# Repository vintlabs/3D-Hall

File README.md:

# 3D-Hall
3D Hall Effect Sensor Module - ALS31313 (Hardware)

This I²C sensor module cn detect magnetism in three dimensions (XYZ), and can be easily connect to a 3.3V Arduino, ESP32, Raspberry Pi or other microcontrollers. The header is designed such that it can plug directly into the header of a Raspberry Pi or and ESP32-Zip module. Board dimensions: 40mm x 15mm

The default I2C address is 0x60, but can be changed by modifying R3-R6 (See page 22 of the ALS31313 datasheet (https://www.allegromicro.com/~/media/Files/Datasheets/ALS31313-Datasheet.ashx).

Example Aruino sketch: https://github.com/vintlabs/ESP32-Arduino-3dHall-Example

Currently available on Amazon Canada: https://www.amazon.ca/dp/B0896VD73G

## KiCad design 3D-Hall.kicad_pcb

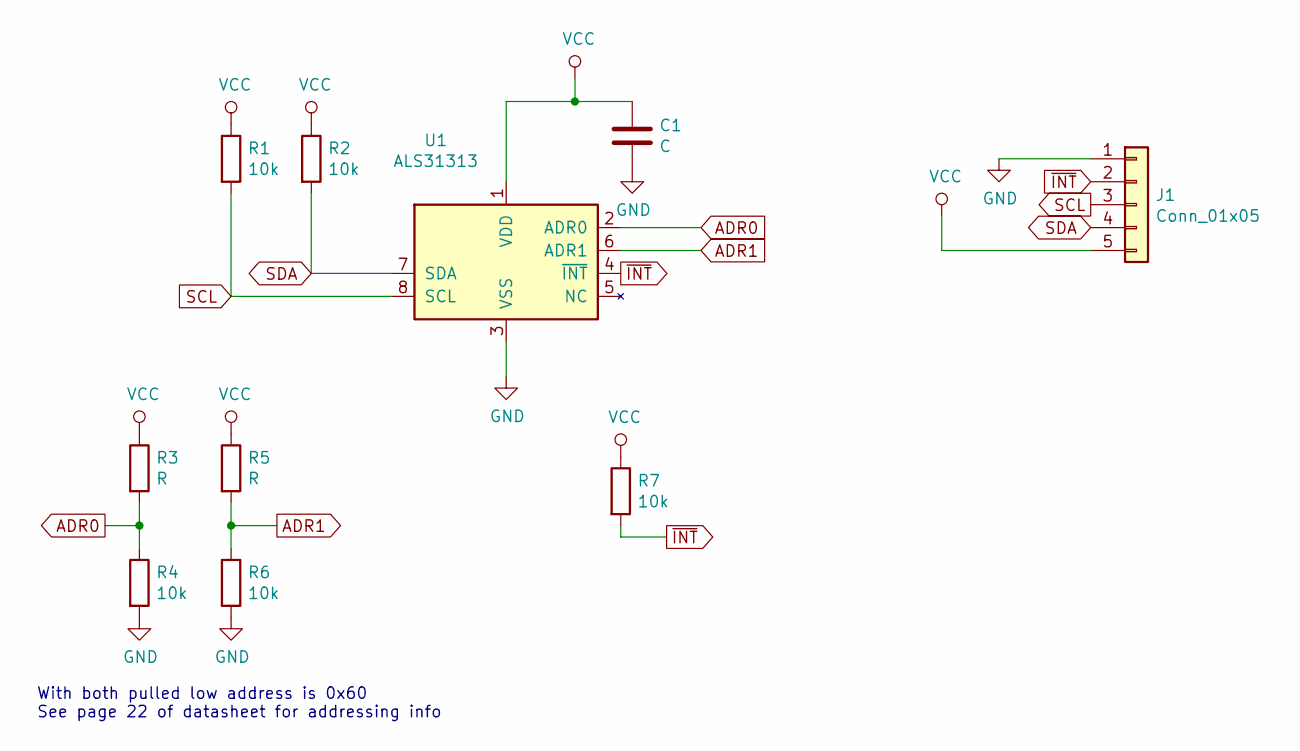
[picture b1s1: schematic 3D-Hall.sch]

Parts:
C1: C; C_0603_1608Metric_Pad1.05x0.95mm_HandSolder
J1: Conn_01x05; PinSocket_1x05_P2.54mm_Horizontal
R1, R2, R4, R6, R7: 10k; R_0805_2012Metric_Pad1.15x1.40mm_HandSolder
R3, R5: R; R_0805_2012Metric_Pad1.15x1.40mm_HandSolder
U1: ALS31313; TSSOP-8_3x3mm_P0.65mm

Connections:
ADR0: R3.2, R4.1, U1.2 (ADR0)
ADR1: R5.2, R6.1, U1.6 (ADR1)
GND: C1.2, J1.1, R4.2, R6.2, U1.3 (VSS)
SCL: J1.3, R1.2, U1.8 (SCL)
SDA: J1.4, R2.2, U1.7 (SDA)
VCC: C1.1, J1.5, R1.1, R2.1, R3.1, R5.1, R7.1, U1.1 (VDD)
~INT: J1.2, R7.2, U1.4 (~INT)

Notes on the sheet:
With both pulled low address is 0x60 See page 22 of datasheet for addressing info

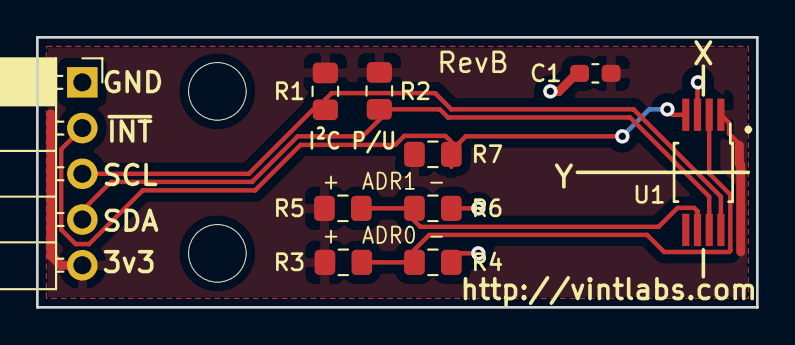
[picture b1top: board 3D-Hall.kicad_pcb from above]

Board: 2 copper layers, 40.0 x 15.0 mm, 10 parts (0 on the bottom side), 7 nets.

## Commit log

2020-06-25 Inital Import (RevB, as sent for manufacture)
2020-07-30 Added image
